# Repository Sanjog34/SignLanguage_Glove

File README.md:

# Smart Glove for Real-Time Nepali Sign Language to Speech Translation

This repository contains the source code, hardware design files, datasets, and documentation for the **Smart Glove for Real-Time Nepali Sign Language (NSL) to Speech Translation** system. Developed as a final engineering project at Pashchimanchal Campus, Tribhuvan University, this wearable system translates static and dynamic Nepali Sign Language gestures into spoken audio output in real time to bridge the communication gap between the deaf/hard-of-hearing community and non-signers.

---

## Table of Contents
- [Abstract](#abstract)
- [System Architecture](#system-architecture)
- [Hardware & Software Requirements](#hardware--software-requirements)
- [Methodology](#methodology)
  - [Hardware Interfacing & Sensor Calibration](#hardware-interfacing--sensor-calibration)
  - [Data Collection & Dataset Preparation](#data-collection--dataset-preparation)
  - [Model Architecture & Training](#model-architecture--training)
  - [Real-Time Inference Pipeline](#real-time-inference-pipeline)
  - [Text-to-Speech (TTS) Integration](#text-to-speech-tts-integration)
- [Results and Discussion](#results-and-discussion)
  - [Real-Time Performance](#real-time-performance)
  - [Random Forest Analysis](#random-forest-analysis)
  - [LSTM Model Analysis](#lstm-model-analysis)
- [Video Demo](#video-demo)
- [Project Report](#project-report)
- [Appendix](#appendix)

---

## Abstract

Communication is essential, yet most non-signers in Nepal do not understand Nepali Sign Language (NSL). This project presents a wearable smart glove system integrating **8 flex sensors** (capturing joint flexion across MCP and PIP finger joints) and an **MPU6050 6-axis IMU** mounted on an **ESP32 microcontroller**. Sensor data is transmitted via Bluetooth to a host environment, where a dual machine learning model pipeline performs real-time classification:
- **Random Forest Classifier**: Handles 9 static gestures (4 alphabets: *ka, kha, ga, gha, nga* and 4 numerals: *ek, dui, tin, char*) with **99.56% test accuracy**.
- **2-Layer LSTM Network**: Processes 7 dynamic gestures (*namaste, mero, naam, sanjog, ho, malai, chinnu*) forming a basic self-introduction sequence, achieving **~94% validation accuracy**.

Across 320 real-time trials, the full system achieved an overall accuracy of **93.1%**, with average translation latencies of **0.5 seconds** for static gestures and **~2.0 seconds** for dynamic gestures.

---

## System Architecture

```
+-------------------------------------------------------------+
|                     WEARABLE SMART GLOVE                    |
|  [8x Flex Sensors (PIP/MCP Joints)]  [MPU6050 6-Axis IMU]   |
+------------------------------+------------------------------+
                               | Analog/I2C
                               v
+-------------------------------------------------------------+
|                     ESP32 MICROCONTROLLER                   |
|   - Signal Acquisition & Filtering                          |
|   - Feature Vector Assembly & Gyroscope Accumulation        |
+------------------------------+------------------------------+
                               | Bluetooth Serial Stream
                               v
+-------------------------------------------------------------+
|                      HOST COMPUTER                          |
|  +-------------------------------------------------------+  |
|  |             Motion Detection Logic                    |  |
|  |     (Rolling Buffer Gyro Variance Thresholding)       |  |
|  +---------------------------+---------------------------+  |
|                              |                              |
|              +---------------+---------------+              |
|              | Static                        | Dynamic      |
|              v                               v              |
|   +---------------------+         +---------------------+   |
|   | Random Forest Model |         | 2-Layer LSTM Model  |   |
|   |  (Static Gestures)  |         | (Dynamic Sequences) |   |
|   +----------+----------+         +----------+----------+   |
|              |                               |              |
|              +---------------+---------------+              |
|                              | Predicted Label              |
|                              v                              |
|   +-----------------------------------------------------+   |
|   |         Pre-generated Nepali Audio Retrieval        |   |
|   |                 (gTTS / MP3 Playback)               |   |
|   +--------------------------+--------------------------+   |
+------------------------------|------------------------------+
                               v
                     (( Speaker Output ))
```

---

## Hardware & Software Requirements

### Hardware Components
- **ESP32 Microcontroller**: Dual-core SoC handling ADC acquisition, I2C IMU sampling, and Bluetooth RFCOMM streaming.
- **Flex Sensors (x8)**: Variable bend-resistors positioned across finger joints (2.2" and 4.5" strips).
- **MPU6050 IMU**: 3-axis accelerometer + 3-axis gyroscope for hand orientation and motion tracking.
- **Resistors**: $20	\text{ k}\Omega$ precision fixed series resistors for flex sensor voltage dividers.
- **Audio Output Device**: Speaker/headphones connected to the host system.

### Software & Libraries
- **Firmware**: C++ / Arduino Framework deployed via **PlatformIO** / **VS Code**.
- **Data Processing & ML/DL**: Python 3.x, `NumPy`, `Pandas`, `Scikit-Learn`, `TensorFlow / Keras`.
- **Text-to-Speech**: `gTTS` (Google Text-to-Speech) library.
- **Hardware CAD**: KiCad EDA for schematic capture and PCB layout.

---

## Methodology

### Hardware Interfacing & Sensor Calibration
- **Flex Sensor Placement**: 8 flex sensors are mapped to capture fine-grained finger articulation:
  - **Index, Middle, Ring Fingers**: 2 sensors per finger—one across the Proximal Interphalangeal (PIP / "Up") joint and one across the Metacarpophalangeal (MCP / "Low") joint (`idxUp`, `idxLow`, `midUp`, `midLow`, `ringUp`, `ringLow`).
  - **Thumb & Pinky**: 1 sensor each (`thumb`, `pinky`).
- **Voltage Divider Optimization**: Flex resistance ranges from $\sim 20	\text{ k}\Omega$ (flat) to $\sim 24	\text{ k}\Omega$ (bent). Connecting a $20	\text{ k}\Omega$ series resistor ($R_2$) maximizes the ADC voltage differential to optimize 12-bit ADC sensitivity.
- **Sensor Calibration**: Physical conditioning (15–20 fist flexes) redistributes sensor conductive ink before use. At startup, the system captures 100 baseline idle samples to compute per-sensor zero offsets.

### Data Collection & Dataset Preparation
Sampling is executed at **60 ms intervals**. Each feature vector consists of 17 parameters:

`x = [idxUp, idxLow, midUp, midLow, ringUp, ringLow, thumb, pinky, a_x, a_y, a_z, g_x, g_y, g_z, acc_g_x, acc_g_y, acc_g_z]`

- **Static Dataset**: 1000 samples per gesture across 9 gestures = **9,000 labeled samples** (`.csv` format). Dynamic gyro parameters were excluded during static training.
- **Dynamic Dataset**: Motion detection uses a 20-sample rolling buffer tracking accumulated gyroscope variances ($\Delta acc_g$). A threshold $> 20$ triggers active recording, terminating after 7 consecutive static samples. 200 raw sequences per gesture were recorded and expanded to **1,500 samples per gesture** via white-noise data augmentation. All sequences were resampled to a fixed length of **70 frames** using linear interpolation.

---

### Model Architecture & Training

1. **Static Gestures (Random Forest Classifier)**
   - Input scaled via `StandardScaler`. Hyperparameters tuned using `GridSearchCV`.
   - **Configuration**: `n_estimators=30`, `max_samples=0.70`, Train/Test Split: 70/30.
   
2. **Dynamic Gestures (LSTM Network)**
   - $(70 \text{ frames} \times 15 \text{ features})$, normalized via `MinMaxScaler`.
   - **Architecture**: 2-layer stacked LSTM (16 hidden units per layer), Dropout rate $= 0.5$, Batch size $= 32$, Adam optimizer, Categorical Cross-Entropy loss.
   - **Early Stopping**: Monitored validation loss with a patience of 10 epochs.

---

### Real-Time Inference Pipeline
1. ESP32 streams sensor vectors via Bluetooth RFCOMM.
2. Host Python script buffers incoming frames and evaluates gyroscope variance:
   - **Low Variance ($\le 20$)**: Routes current frame to Random Forest (`.joblib`) $
ightarrow$ Output static gesture.
   - **High Variance ($> 20$)**: Accumulates sequence frame buffer $
ightarrow$ Interpolates to 70 frames $
ightarrow$ Feeds into LSTM (`.h5`) $
ightarrow$ Output dynamic gesture.

### Text-to-Speech (TTS) Integration
Predicted labels map to pre-synthesized Devanagari audio files generated via the `gTTS` library. The system executes immediate audio playback upon gesture classification completion.

---

## Results and Discussion

### Real-Time Performance
The complete hardware-software system was evaluated across **320 real-time trials** (20 trials per gesture across 16 gestures).

| Gesture Class | Gesture Type | Correct | Incorrect | Accuracy (%) |
| :--- | :--- | :---: | :---: | :---: |
| **Namaste** | Dynamic | 15 | 5 | 75.0% |
| **Mero** | Dynamic | 16 | 4 | 80.0% |
| **Naam** | Dynamic | 20 | 0 | 100.0% |
| **Sanjog** | Dynamic | 18 | 2 | 90.0% |
| **Ho** | Dynamic | 20 | 0 | 100.0% |
| **Malai** | Dynamic | 18 | 2 | 90.0% |
| **Chinnu** | Dynamic | 19 | 1 | 95.0% |
| **ek (1)** | Static | 19 | 1 | 95.0% |
| **dui (2)** | Static | 20 | 0 | 100.0% |
| **tin (3)** | Static | 20 | 0 | 100.0% |
| **char (4)**| Static | 17 | 3 | 85.0% |
| **ka** | Static | 20 | 0 | 100.0% |
| **kha** | Static | 20 | 0 | 100.0% |
| **ga** | Static | 18 | 2 | 90.0% |
| **gha** | Static | 18 | 2 | 90.0% |
| **nga** | Static | 20 | 0 | 100.0% |
| **OVERALL** | **System Total** | **298** | **22** | **93.1%** |

- **Average Static Latency**: $\sim 0.5 	\text{ seconds}$
- **Average Dynamic Latency**: $\sim 2.0 	\text{ seconds}$

### Random Forest Analysis
- **Training Accuracy**: 99.94%
- **Testing Accuracy**: 99.56%
- **Out-Of-Bag (OOB) Score**: 99.62%

The minimal delta between training and test metrics confirms high model generalization with minimal risk of overfitting.

### LSTM Model Analysis
- **Validation Accuracy**: Stabilized at $\sim 94\%$.
- **Temporal Importance Analysis**: Feature importance evaluation revealed that the network heavily weights the final sequence steps (frames 66–69), focusing on "ending signatures." This temporal weighting explains occasional misclassifications between gestures with similar trajectory endings (e.g., *mero* vs. *namaste*). Future work will incorporate **Attention Mechanisms** or **Bidirectional LSTMs (BiLSTM)** to distribute importance evenly across full trajectories.

---

## Video Demo

An end-to-end video demonstration showing real-time sign recognition, dual-model inference switching, and instant audio vocalization is available below:

[Watch Demo Video](docs/demo.mp4)

---

## Project Report

The complete academic major project report submitted to the Department of Electronics and Computer Engineering, Pashchimanchal Campus, IOE, Tribhuvan University, is included in this repository:

📄 **[Download Full Major Project Report (PDF)](docs/Major_Project_Report.pdf)**

---

## Appendix

### Prototype Smart Glove
Physical wearable prototype featuring 8 integrated flex sensors, custom wiring harness, and glove-mounted ESP32/MPU6050 enclosure.

---

### Custom PCB Schematic
KiCad EDA PCB schematic showing power regulation, ESP32 ADC pin routing for flex sensor voltage dividers, and I2C lines for MPU6050.

---

## Authors & Acknowledgments
**Project Team (PAS078BEI Batch):**
- [Ganesh Rokaya](https://github.com/Torngt) (PAS078BEI013)
- [Sanjog Sapkota](https://github.com/Sanjog34) (PAS078BEI034)
- [Santosh Kumar Barai](https://github.com/Skbarai) (PAS078BEI035)
- [Upendra Raj Joshi](https://github.com/Upendra48) (PAS078BEI046)

**Supervisor:** Asst. Prof. Khem Raj Koirala  
**Department:** Department of Electronics and Computer Engineering, Pashchimanchal Campus, IOE, Tribhuvan University.

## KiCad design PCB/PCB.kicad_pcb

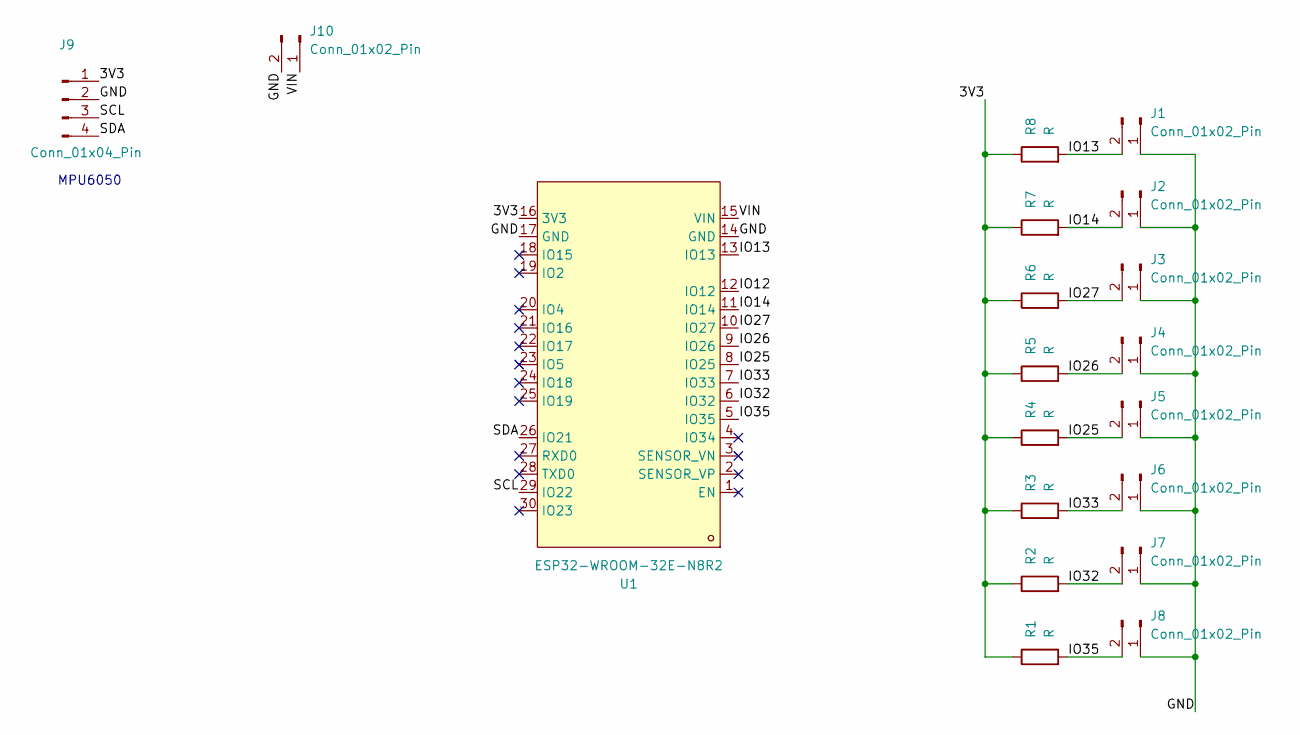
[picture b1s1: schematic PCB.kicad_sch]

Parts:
J1, J2, J3, J4, J5, J6, J7, J8: Conn_01x02_Pin; PinHeader_1x02_P2.54mm_Vertical smd custom
J9: Conn_01x04_Pin; PinHeader_1x04_P2.54mm_Vertical
J10: Conn_01x02_Pin; PinHeader_1x02_P2.54mm_Horizontal
R1, R2, R3, R4, R5, R6, R7, R8: R; R_Axial_DIN0207_L6.3mm_D2.5mm_P10.16mm_Horizontal
U1: ESP32-WROOM-32E-N8R2; esp32 dev board; LCSC Part C5361945

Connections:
/3V3: J9.1, R1.1, R2.1, R3.1, R4.1, R5.1, R6.1, R7.1, R8.1, U1.16 (3V3)
/GND: J1.1, J2.1, J3.1, J4.1, J5.1, J6.1, J7.1, J8.1, J9.2, J10.2, U1.14 (GND), U1.17 (GND)
/IO12: U1.12 (IO12)
/IO13: J1.2, R8.2, U1.13 (IO13)
/IO14: J2.2, R7.2, U1.11 (IO14)
/IO25: J5.2, R4.2, U1.8 (IO25)
/IO26: J4.2, R5.2, U1.9 (IO26)
/IO27: J3.2, R6.2, U1.10 (IO27)
/IO32: J7.2, R2.2, U1.6 (IO32)
/IO33: J6.2, R3.2, U1.7 (IO33)
/IO35: J8.2, R1.2, U1.5 (IO35)
/SCL: J9.3, U1.29 (IO22)
/SDA: J9.4, U1.26 (IO21)
/VIN: J10.1, U1.15 (VIN)

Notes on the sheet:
MPU6050

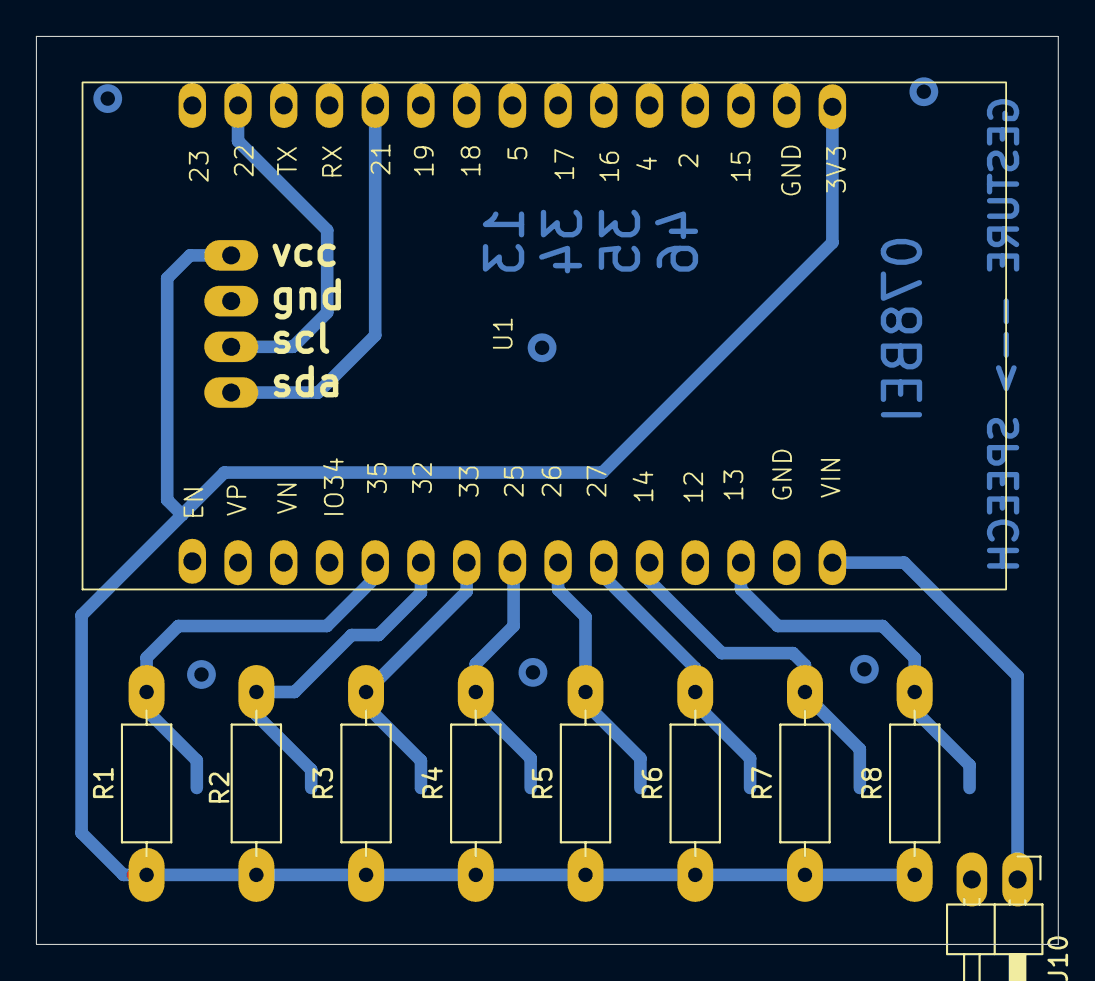
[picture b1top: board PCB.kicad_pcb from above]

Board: 2 copper layers, 56.8 x 50.4 mm, 19 parts (0 on the bottom side), 13 nets.

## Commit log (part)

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2025-12-09 updayes
2026-05-14 Revise README for Sign Language Glove project
    Updated project description and added detailed sections on tech stack, repository structure, data flow, setup, and ML pipeline.
2026-05-15 static_dynamic prediction pipeline
2026-05-16 fixes
2026-05-17 bluetooth data transfer
2026-06-05 cleaned
2026-06-05 added images
